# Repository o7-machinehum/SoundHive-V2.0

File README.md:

SoundHive - V2.0
=========

SoundHive is a low cost open source audio amplifier, designed to be stacked much like Arduino, the
aim is to reduce electronic waste by utilizing existing speakers. It's too common for people to buy 
a new home theatre system and dispose of the old equiptment, which ends up directly in a landfill.

The reality is that most of the speakers made ~20 years ago are high quality wooden builds, 
that sound awesome and simply can't be replaced by their shiny new plastic childen.

Soundhive also increased modularity and customization. This allows the greater flexibility.

V2.0 is an evolution of the original project, which can be found here: https://github.com/Machine-Hum/SoundHive

Amp - 40W
--------
Boards just came in, parts ordered!

-Walker (Machinehum)

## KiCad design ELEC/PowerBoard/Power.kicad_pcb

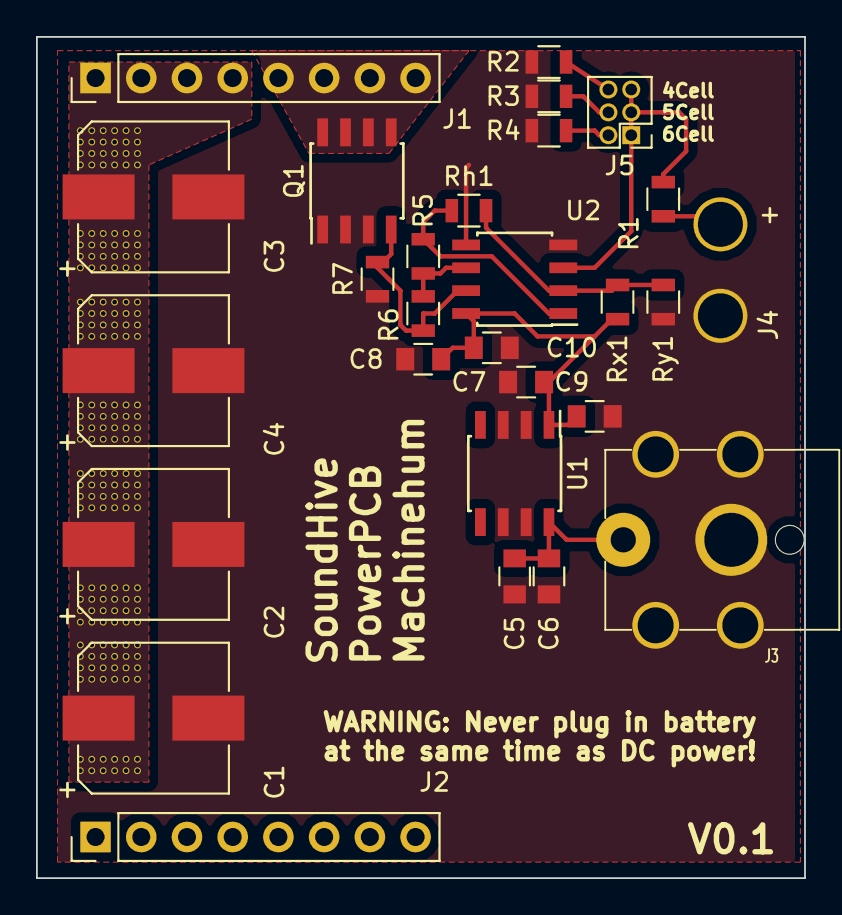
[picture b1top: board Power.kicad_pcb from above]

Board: 2 copper layers, 42.7 x 46.7 mm, 28 parts (0 on the bottom side), 12 nets.

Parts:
C1, C2, C3, C4: 220uF; CP_Elec_8x10.5
C5, C7, C9: 100nF; C_0805
C6, C8: 10uF; C_0805
C10: 1uF; C_0805
J1, J2: CONN_01X08; Pin_Header_Straight_1x08_Tall_Pitch2.54mm
J3: Barrel_Jack; PJ-082BH
J4: XT60 Connector; XT60_Inline
J5: CONN_02X03; Pin_Header_Straight_2x03_Pitch1.27mm
Q1: MOSFET_8PIN; SOIC-8_3.9x4.9mm_Pitch1.27mm
R1, R5, R6, R7: 1M; R_0805
R2: 422K; R_0805
R3: 316K; R_0805
R4: 243K; R_0805
Rh1: 1.32M; R_0805
Rx1: 220K; R_0805
Ry1: 1M; R_0805
U1: LM9036MX; SOIC-8_3.9x4.9mm_Pitch1.27mm
U2: LMV358; SOIC-8_3.9x4.9mm_Pitch1.27mm

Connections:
+5V: C7.1, C8.1, C9.1, C10.1, Rx1.1, U1.1, U2.8
+24V: C1.1, C2.1, C3.1, C4.1, C5.1, C6.1, J1.1, J1.2, J1.3, J1.4, J3.1, J4.1, R1.1, U1.8
GND: C1.2, C2.2, C3.2, C4.2, C5.2, C6.2, C7.2, C8.2, C9.2, C10.2, J3.2, J4.2, Q1.1, Q1.2, Q1.3, R2.2, R3.2, R4.2, R7.1, Ry1.2, U1.2, U1.3, U1.6, U1.7, U2.4, U2.5
unnamed: J1.5, J1.6, J1.7, J1.8, Q1.5, Q1.6, Q1.7, Q1.8
unnamed: J5.2, R4.1
unnamed: J5.4, R3.1
unnamed: J5.6, R2.1
unnamed: Q1.4, R6.1, R7.2, U2.7
unnamed: R5.1, R6.2, U2.6
unnamed: R5.2, Rh1.1, U2.1
unnamed: Rh1.2, Rx1.2, Ry1.1, U2.2
Vref: J5.1, J5.3, J5.5, R1.2, U2.3

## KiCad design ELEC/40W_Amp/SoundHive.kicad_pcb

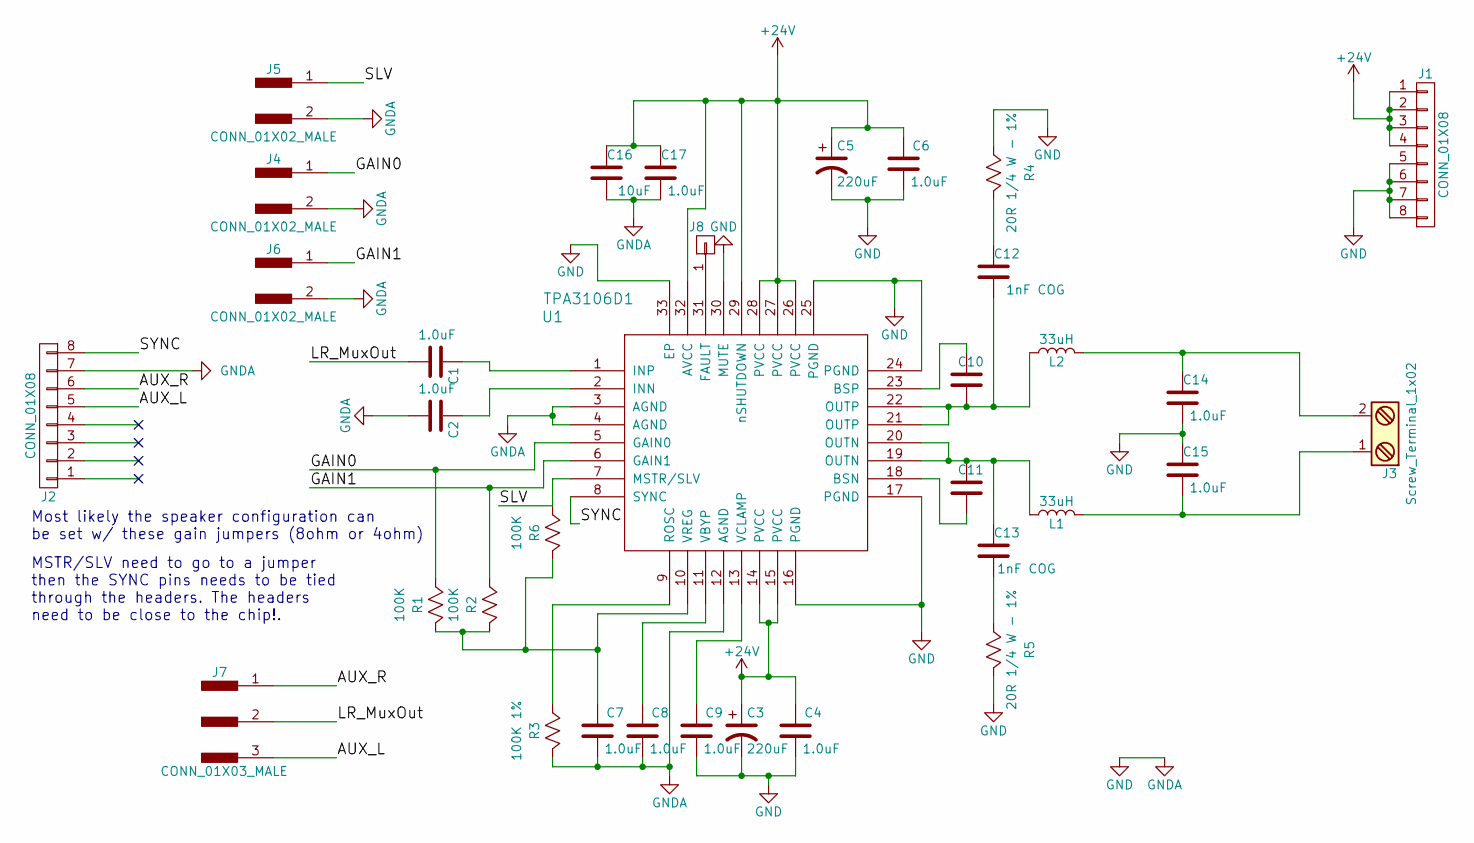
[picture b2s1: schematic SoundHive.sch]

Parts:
C1, C2, C4, C6, C7, C8, C9, C14, C15, C17: 1.0uF; C_0805; Part Number UMK212BJ105KG-T
C3, C5: 220uF; CP_Elec_8x10.5; Part Number EEE-1VA221UP
C10, C11: 0.22uF; C_0805; Part Number UMK212B7224KG-T
C12, C13: 1nF COG; C_0805; Part Number C0805C102J5GACTU
C16: 10uF; C_0805; Part Number GRM21BR6YA106KE43L
J1, J2: CONN_01X08; Pin_Header_Straight_1x08_Tall_Pitch2.54mm
J3: Screw_Terminal_1x02; TerminalBlock_OSTTC022162; Part Number 1715721
J4, J5, J6: CONN_01X02_MALE; Pin_Header_Angled_1x02_Pitch2.54mm
J7: CONN_01X03_MALE; Pin_Header_Angled_1x03_Pitch2.54mm
J8: CONN_01X01; 10mil_Via
L1: 33uH; XAL6060-333ME; Part Number XAL6060-333ME
L2: 33uH; XAL6060-333ME; Part Number 33uH
R1, R2, R6: 100K; R_0805; Part Number RMCF0805JT100K
R3: 100K 1%; R_0805; Part Number RC0805FR-07100KL
R4, R5: 20R 1/4 W - 1%; R_1206; Part Number RC0805FR-0720RL
U1: TPA3106D1; LQFP-32_7x7mm_Pitch0.8mm-EP; Part Number TPA3106D1

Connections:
+24V: C3.1, C4.2, C5.1, C6.2, C16.2, C17.2, J1.1, J1.2, J1.3, J1.4, U1.14 (PVCC), U1.15 (PVCC), U1.26 (PVCC), U1.27 (PVCC), U1.28 (PVCC), U1.29 (nSHUTDOWN), U1.32 (AVCC)
/AUX_L: J2.5, J7.3
/AUX_R: J2.6, J7.1
/GAIN0: J4.1, R1.1, U1.5 (GAIN0)
/GAIN1: J6.1, R2.1, U1.6 (GAIN1)
/LR_MuxOut: C1.2, J7.2
/SLV: J5.1, R6.1, U1.7 (MSTR/SLV)
/SYNC: J2.8, U1.8 (SYNC)
GND: C2.2, C3.2, C4.1, C5.2, C6.1, C7.1, C8.1, C9.1, C14.1, C15.2, C16.1, C17.1, J1.5, J1.6, J1.7, J1.8, J2.7, J4.2, J5.2, J6.2, R3.2, R4.1, R5.2, U1.3 (AGND), U1.4 (AGND), U1.12 (AGND), U1.16 (PGND), U1.17 (PGND), U1.24 (PGND), U1.25 (PGND), U1.30 (MUTE), U1.33 (EP)
unnamed: C1.1, U1.1 (INP)
unnamed: C2.1, U1.2 (INN)
unnamed: C7.2, R1.2, R2.2, R6.2, U1.10 (VREG)
unnamed: C8.2, U1.11 (VBYP)
unnamed: C9.2, U1.13 (VCLAMP)
unnamed: C10.1, C12.1, L2.1, U1.21 (OUTP), U1.22 (OUTP)
unnamed: C10.2, U1.23 (BSP)
unnamed: C11.1, U1.18 (BSN)
unnamed: C11.2, C13.2, L1.1, U1.19 (OUTN), U1.20 (OUTN)
unnamed: C12.2, R4.2
unnamed: C13.1, R5.1
unnamed: C14.2, J3.2, L2.2
unnamed: C15.1, J3.1, L1.2
unnamed: J8.1, U1.31 (FAULT)
unnamed: R3.1, U1.9 (ROSC)

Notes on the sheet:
Most likely the speaker configuration can be set w/ these gain jumpers (8ohm or 4ohm)
MSTR/SLV need to go to a jumper then the SYNC pins needs to be tied through the headers. The headers need to be close to the chip!.

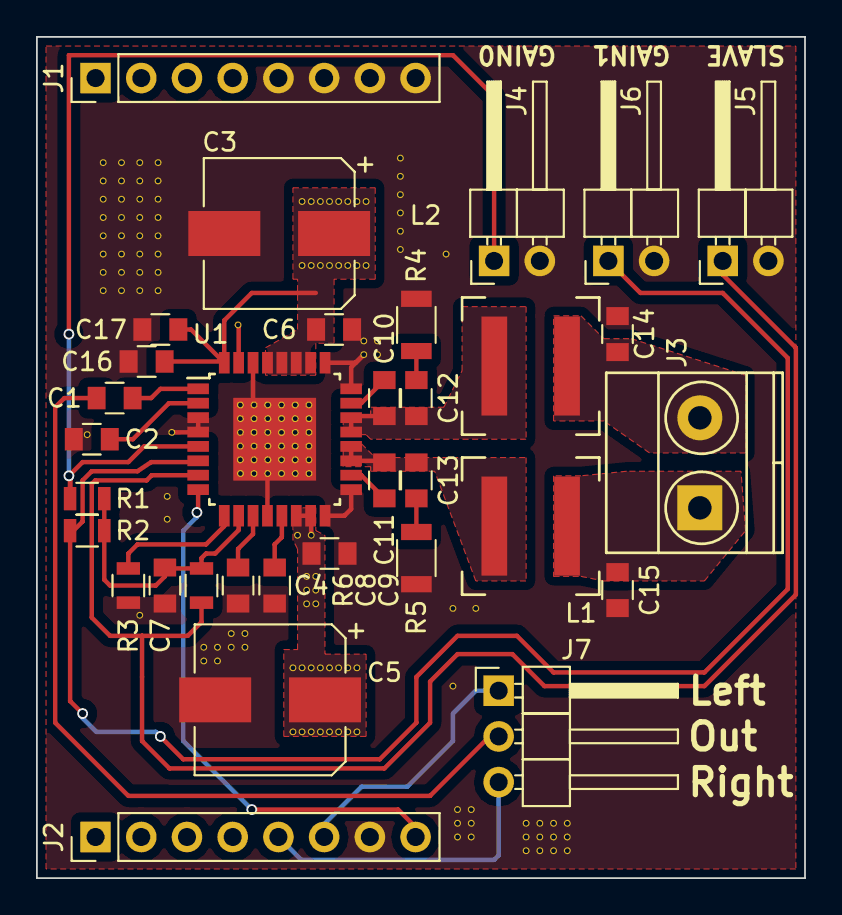
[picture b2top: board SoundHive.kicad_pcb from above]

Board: 2 copper layers, 42.7 x 46.7 mm, 34 parts (0 on the bottom side), 24 nets.

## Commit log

2017-05-26 Getting started
2017-06-01 Updated Notes a bit
2017-06-01 Notes
2017-06-01 Added files
2017-06-02 Redecorating
2017-06-02 Cleanup
2017-06-06 Paths updated and stuff
2017-06-06 -Still rolling
2017-06-06 Parts and stuff
2017-06-07 Make sure when cloning into the parts directory from the kicad master you delete the tracking info before actually commiting, or else it will add it as a submodule
2017-06-07 Added more parts, make so you don't add git submodules
2017-06-07 Added pin header library
2017-06-07 Layout changes, Tall headers added
2017-06-07 Major work.
2017-06-09 Changed paths (Used ${KIPRJMOD})
2017-06-12 Added connector, redecorated.
    Consider changing 2.54mm pich headers to somethin smaller
2017-06-12 Create README.md
    Spelling
2017-06-12 Create Notes
    Connector P/N
2017-06-13 -Moved all 3D models into project -This should be how we move forward. System paths are too flakey
2017-06-15 V1.01, board ordered. June 14th, 2017, OSH Park.
2017-06-15 Create README.md
    Changes to readme
2017-06-20 Added new project for power board, started adding components
2017-06-21 Working on the power board
2017-07-02 Added some images, updated README
2017-07-02 Plotted
2017-07-07 Added CSV
2017-07-09 Changed notes file. Connector Issues
2017-07-09 Added roadmap, worked on power board
2017-07-20 Worked on power distrobution PCB
2017-07-26 Added some notes
2017-07-26 Traded connector for something that actually fits
2017-07-26 Producted 3D model output
2017-07-26 Added StepUP to filesystem, this should be used for the next PCB
2017-07-27 Added dimensions, re-rendered PCB
2017-07-28 Filled out parts - digi parts ordered
2017-07-28 Changed some stuff on the 3D model
2017-07-28 Added Step file
2017-08-07 Matlab file for low battery cutoff
2017-08-09 Did a whole whack on the power PCB
2017-08-11 Finished Power PCB
2017-08-11 Added some plots
2017-08-11 Added 3D image
2017-08-11 Added more plots
2017-08-15 -Filled in P/N -Generated BOM -Ordered PCBs
